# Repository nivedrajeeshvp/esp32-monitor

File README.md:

# Nexus Monitor — ESP32 Gas & Environmental Monitoring System

An ESP32-based embedded IoT project integrating multi-gas sensing, temperature and humidity monitoring, custom PCB design, and a web-based monitoring dashboard.

<p align="center">
  <strong>Embedded Systems · IoT · PCB Design · Sensor Integration</strong>
</p>

---

## Overview

**Nexus Monitor** is an ESP32-based gas and environmental monitoring system designed to acquire sensor readings and present monitoring data through a web interface.

The system integrates MQ-series gas sensors, an SHT31 temperature and humidity sensor, ESP32 analog and I²C interfaces, Wi-Fi connectivity, an HTTP API, and a web dashboard. The hardware design includes a custom circuit schematic and PCB layout created using KiCad.

The project combines embedded firmware development, electronic circuit design, sensor interfacing, and web technologies in a single platform.

## Key Features

- **Multi-gas sensing:** Interfaces with MQ-3, MQ-137, and MQ-138 gas sensor modules.
- **Environmental monitoring:** Uses the SHT31 sensor for temperature and relative humidity measurements.
- **ADC acquisition:** Reads analog signals from gas sensor modules through the ESP32 ADC.
- **I²C communication:** Interfaces with the SHT31 sensor.
- **Wireless connectivity:** Supports ESP32 Wi-Fi access point operation.
- **HTTP API:** Makes sensor data available to the web interface.
- **Web dashboard:** Displays sensor telemetry using HTML, CSS, and JavaScript.
- **LittleFS integration:** Supports storing web assets in the ESP32 flash filesystem.
- **Custom PCB design:** Includes circuit schematic development and PCB layout in KiCad.
- **PlatformIO workflow:** Supports firmware building and uploading through PlatformIO.

## Project Screenshots

### Web Dashboard

*Dashboard interface displaying simulated sensor readings in local demo mode. These values are illustrative and are not confirmed live hardware measurements.*

### Circuit Schematic

*Circuit design showing the ESP32 development board, MQ-series gas sensor connectors, SHT31 interface, and LM2596-based power supply.*

### PCB Layout

*PCB layout showing the ESP32 footprint, gas sensor connectors, power supply components, and routed connections.*

## Hardware Components

| Component | Purpose |
|---|---|
| ESP32 DevKit | Main microcontroller and Wi-Fi connectivity |
| MQ-3 gas sensor | Gas-sensing input |
| MQ-137 gas sensor | Gas-sensing input |
| MQ-138 gas sensor | Gas-sensing input |
| SHT31 sensor | Temperature and relative humidity measurement |
| LM2596-based buck converter | DC-DC power conversion circuit |
| Passive components | Filtering, voltage conditioning, and circuit support |
| Custom PCB | Integration of the microcontroller and sensor interfaces |

*Verify component variants and circuit ratings against the actual schematic and datasheets before assembling or powering the hardware.*

## Software and Technologies

- **Programming:** C, C++, Embedded C
- **Microcontroller:** ESP32
- **Framework:** Arduino
- **Build system:** PlatformIO
- **Sensor libraries:** Adafruit SHT31 Library, Adafruit BusIO
- **Communication:** ADC, I²C, Wi-Fi, HTTP
- **Web development:** HTML5, CSS3, JavaScript
- **Embedded filesystem:** LittleFS
- **Electronic design automation:** KiCad
- **Version control:** Git and GitHub
- **Deployment:** Vercel for the existing web dashboard

## System Architecture

```text
 MQ-3 Gas Sensor ─────┐
 MQ-137 Gas Sensor ───┼──> ESP32 ADC ────────┐
 MQ-138 Gas Sensor ───┘                      │
                                             │
 SHT31 Sensor ─────────── I²C ───────────────┤
                                             ▼
                                    ESP32 Firmware
                                             │
                                      Wi-Fi / HTTP
                                             │
                                             ▼
                                       Web Dashboard

 LM2596 Power Supply ─────> Power Rails
 KiCad Schematic ─────────> PCB Layout
```

The ESP32 firmware handles sensor acquisition and communication. The dashboard presents data supplied by the configured interface. Actual live monitoring depends on the firmware, API, and dashboard being correctly integrated and running.

## Repository Structure

```text
esp32-monitor/
├── src/
│   └── main.cpp
├── include/
├── lib/
├── test/
├── data/
│   ├── app.js
│   ├── index.html
│   └── style.css
├── docs/
│   └── images/
│       ├── schematic.png
│       ├── pcb-layout.png
│       └── dashboard.png
├── hardware/
│   ├── README.md
│   ├── *.kicad_pro
│   ├── *.kicad_sch
│   └── *.kicad_pcb
├── app.js
├── index.html
├── style.css
├── platformio.ini
├── .gitignore
└── README.md
```

The `hardware/` directory should contain the actual KiCad project files. The screenshot paths under `docs/images/` must match the uploaded filenames.

The root-level dashboard files are retained for the existing web deployment, while the `data/` directory is used for assets intended for the ESP32 LittleFS filesystem.

## Getting Started

### Prerequisites

Install the following tools:

1. [Visual Studio Code](https://code.visualstudio.com/)
2. [PlatformIO IDE](https://platformio.org/install/ide?install=vscode)
3. USB drivers appropriate for your ESP32 development board
4. Git, for cloning and version control

### Clone the Repository

```bash
git clone https://github.com/nivedrajeeshvp/esp32-monitor.git
cd esp32-monitor
```

### PlatformIO Configuration

The project configuration uses the ESP32 DevKit board and the Arduino framework.

```ini
[env:esp32dev]
platform = espressif32
board = esp32dev
framework = arduino

monitor_speed = 115200
board_build.filesystem = littlefs

lib_deps =
    adafruit/Adafruit SHT31 Library
    adafruit/Adafruit BusIO
```

### Build the Firmware

Open the project in VS Code with PlatformIO installed, connect the ESP32 board, and run:

```bash
pio run
```

### Upload the Firmware

Select the correct serial port and upload the compiled firmware:

```bash
pio run --target upload
```

### Upload LittleFS Assets

Place the web assets intended for the ESP32 filesystem in the `data/` directory. Then build and upload the filesystem image:

```bash
pio run --target buildfs
pio run --target uploadfs
```

**Note:** Uploading a new filesystem image replaces the contents of the device's existing LittleFS partition.

### Monitor Serial Output

```bash
pio device monitor
```

The configured serial baud rate is 115200.

## PCB Design

The hardware design is developed using KiCad and includes:

- ESP32 development board connections
- MQ-series gas sensor connectors
- SHT31 temperature and humidity sensor interface
- LM2596-based DC-DC power supply circuit
- Component footprints and PCB routing

The native KiCad files allow the schematic and board layout to be inspected and modified.

Before PCB fabrication, verify component footprints, connector pinouts, trace clearances, current requirements, power ratings, and the regulator circuit against the selected components' datasheets.

## Calibration and Safety

- MQ-series sensors require appropriate preheating and calibration according to their datasheets and intended applications.
- Raw ADC readings are not equivalent to calibrated gas concentrations in ppm.
- Do not report gas concentration values without an appropriate calibration method.
- Verify that every sensor output is compatible with the ESP32 ADC input voltage limits.
- Check the regulator input range, output voltage, current capacity, thermal performance, and component ratings before powering the circuit.
- This prototype should not be treated as a certified gas safety alarm or a replacement for industrial safety equipment.

## Current Project Status

**Development status: In progress.**

The repository includes ESP32 firmware configuration, sensor-interface development, web dashboard assets, and hardware design work.

The dashboard screenshot represents local demo mode with simulated data. Hardware integration, sensor calibration, live end-to-end operation, and PCB validation should only be marked complete after the corresponding tests have been performed.

## Future Improvements

- Complete hardware integration and validate sensor readings.
- Implement and verify the live sensor-data connection between firmware and dashboard.
- Add calibrated gas-concentration estimation where supported.
- Improve measurement filtering and sensor calibration.
- Add historical data logging and trend visualization.
- Document pin mappings, wiring, and the bill of materials.
- Include PCB fabrication outputs after design verification.
- Add firmware build checks and testing documentation.

## Author

**Nived Rajeesh V P**

- GitHub: [@nivedrajeeshvp](https://github.com/nivedrajeeshvp)
- Repository: [esp32-monitor](https://github.com/nivedrajeeshvp/esp32-monitor)
- Live dashboard: [ESP32 Monitor](https://esp32-monitor-eight.vercel.app/)

## License

No license has been specified yet. Add a suitable open-source license if you intend to permit others to reuse, modify, and distribute this project.

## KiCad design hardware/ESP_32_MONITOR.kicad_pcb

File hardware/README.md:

# Hardware Design

This directory contains the KiCad hardware design files for the Nexus Monitor ESP32 Gas and Environmental Monitoring System.

## Design Files

- Schematic (`.kicad_sch`): Circuit diagram and component connections.
- PCB layout (`.kicad_pcb`): Component placement and routing.
- Project file (`.kicad_pro`): KiCad project configuration.

Design files and supporting documentation will be added here as they become available.

## Status

Hardware integration and validation are in progress.

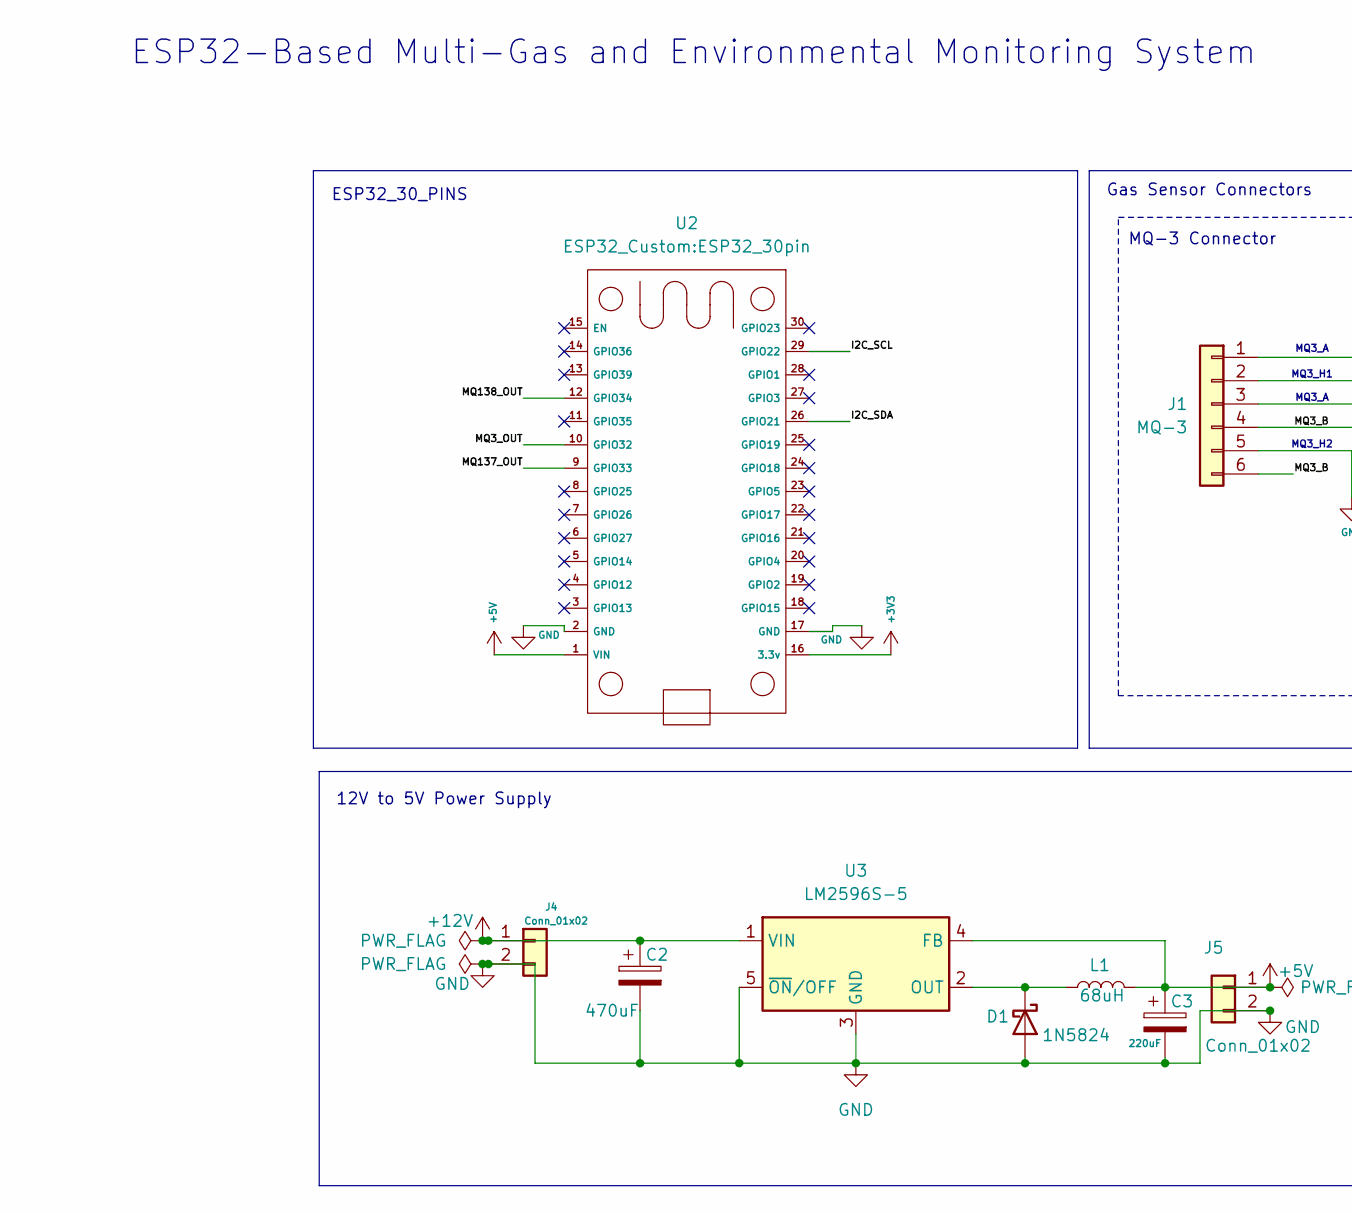
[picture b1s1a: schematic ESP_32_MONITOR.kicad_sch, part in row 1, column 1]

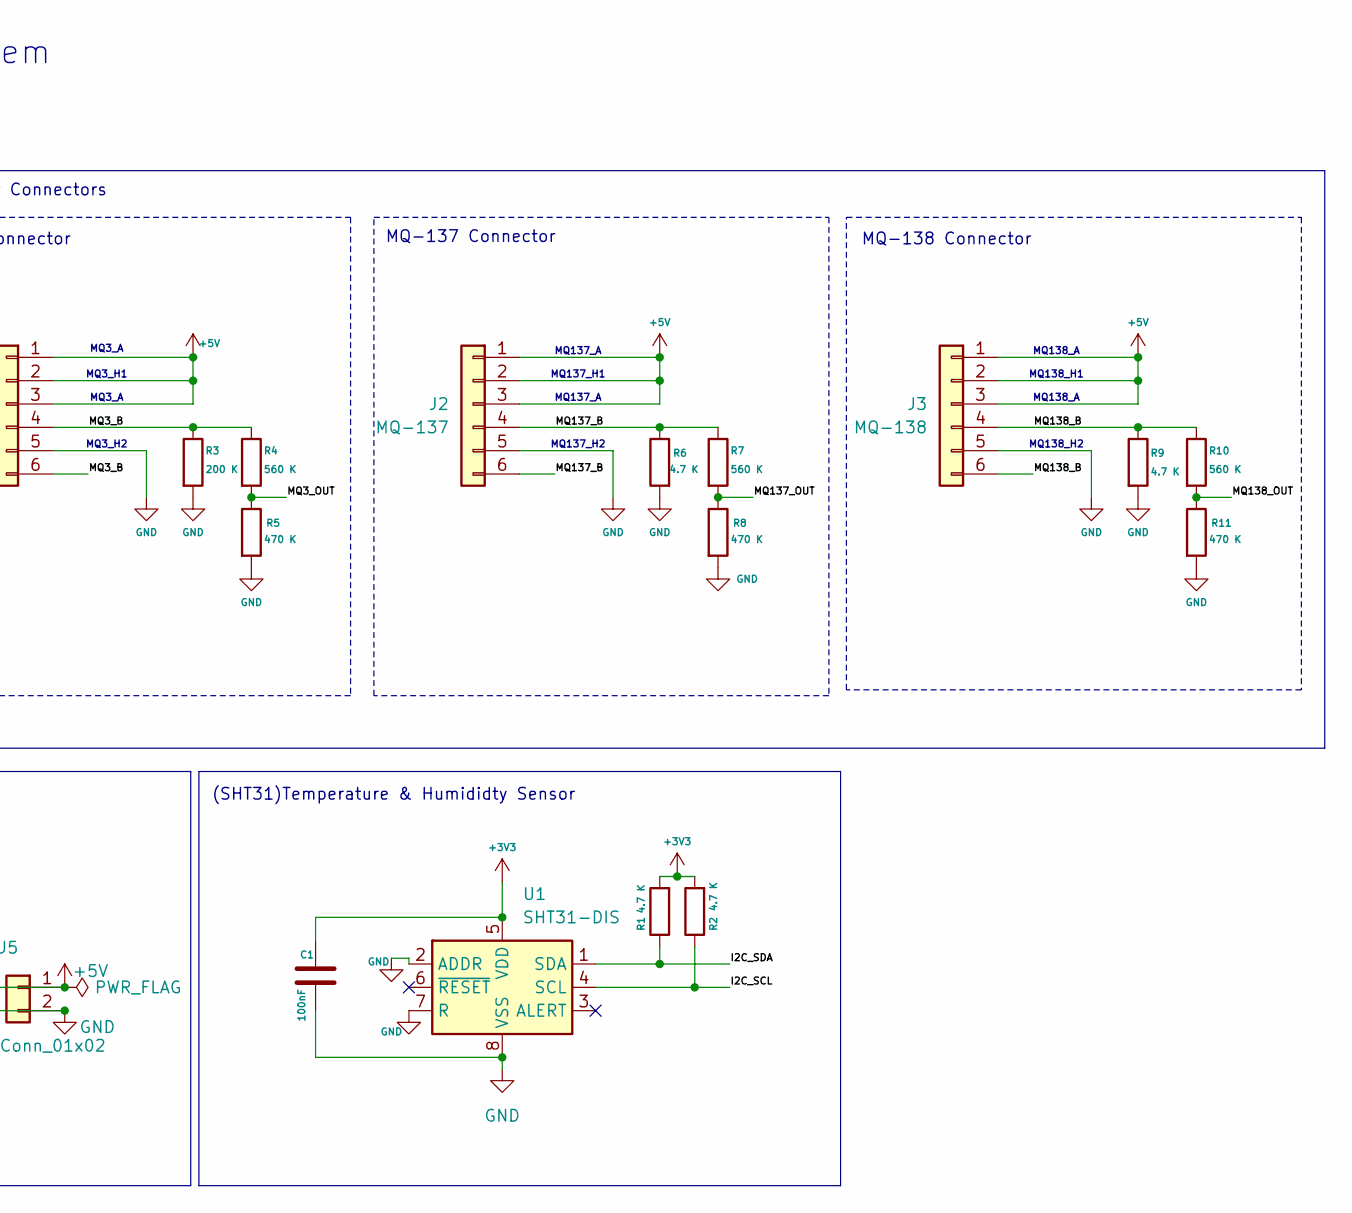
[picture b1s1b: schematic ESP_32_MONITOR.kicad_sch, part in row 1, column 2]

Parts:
C1: 100nF; C_0603_1608Metric
C2: 470uF; CP_Radial_D12.5mm_P5.00mm
C3: 220uF; CP_Radial_D8.0mm_P3.50mm
D1: 1N5824; D_DO-201AD_P15.24mm_Horizontal
J1: MQ-3; MQ-6
J2: MQ-137; MQ-6
J3: MQ-138; MQ-6
J4, J5: Conn_01x02; TerminalBlock_RND_205-00232_1x02_P5.08mm_Horizontal
L1: 68uH; L_Radial_D12.5mm_P7.00mm_Fastron_09HCP
R1, R2, R6, R9: 4.7 K; R_0603_1608Metric
R3: 200 K; R_0603_1608Metric
R4, R7, R10: 560 K; R_0603_1608Metric
R5, R8, R11: 470 K; R_0603_1608Metric
U1: SHT31-DIS; Sensirion_DFN-8-1EP_2.5x2.5mm_P0.5mm_EP1.1x1.7mm
U2: ESP32_30pin
U3: LM2596S-5; TO-263-5_TabPin3

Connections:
+3V3: C1.1, R1.2, R2.2, U1.5 (VDD), U2.16 (3.3v)
+5V: C3.1, J1.1, J1.2, J1.3, J2.1, J2.2, J2.3, J3.1, J3.2, J3.3, J5.1, L1.2, U2.1 (VIN), U3.4 (FB)
+12V: C2.1, J4.1, U3.1 (VIN)
/I2C_SCL: R2.1, U1.4 (SCL), U2.29 (GPIO22)
/I2C_SDA: R1.1, U1.1 (SDA), U2.26 (GPIO21)
/MQ3_B: J1.4, J1.6, R3.1, R4.1
/MQ3_OUT: R4.2, R5.1, U2.10 (GPIO32)
/MQ137_B: J2.4, J2.6, R6.1, R7.1
/MQ137_OUT: R7.2, R8.1, U2.9 (GPIO33)
/MQ138_B: J3.4, J3.6, R9.1, R10.1
/MQ138_OUT: R10.2, R11.1, U2.12 (GPIO34)
GND: C1.2, C2.2, C3.2, D1.2 (A), J1.5, J2.5, J3.5, J4.2, J5.2, R3.2, R5.2, R6.2, R8.2, R9.2, R11.2, U1.2 (ADDR), U1.7 (R), U1.8 (VSS), U1.9 (VSS), U2.2 (GND), U2.17 (GND), U3.3 (GND), U3.5 (~ON/OFF)
unnamed: D1.1 (K), L1.1, U3.2 (OUT)

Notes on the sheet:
MQ3_A
MQ138_H2
MQ-3 Connector
MQ138_A
MQ137_A
12V to 5V Power Supply
MQ138_H1
MQ137_H1
(SHT31)Temperature & Humididty Sensor
ESP32_30_PINS
MQ-138 Connector
MQ3_H1
ESP32-Based Multi-Gas and Environmental Monitoring System
Gas Sensor Connectors
MQ137_H2
MQ3_H2
MQ-137 Connector

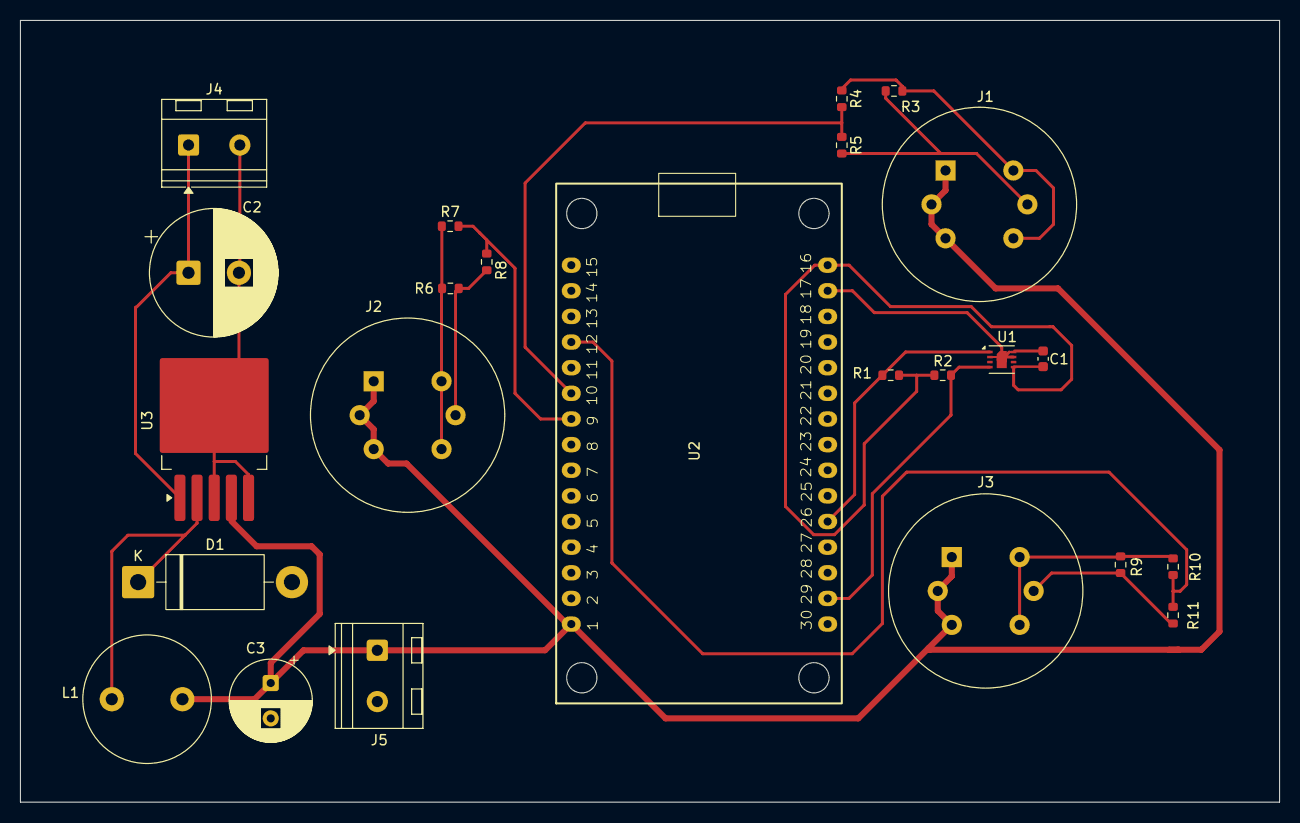
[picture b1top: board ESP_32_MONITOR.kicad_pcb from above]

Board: 2 copper layers, 124.8 x 77.5 mm, 24 parts (0 on the bottom side), 13 nets.
